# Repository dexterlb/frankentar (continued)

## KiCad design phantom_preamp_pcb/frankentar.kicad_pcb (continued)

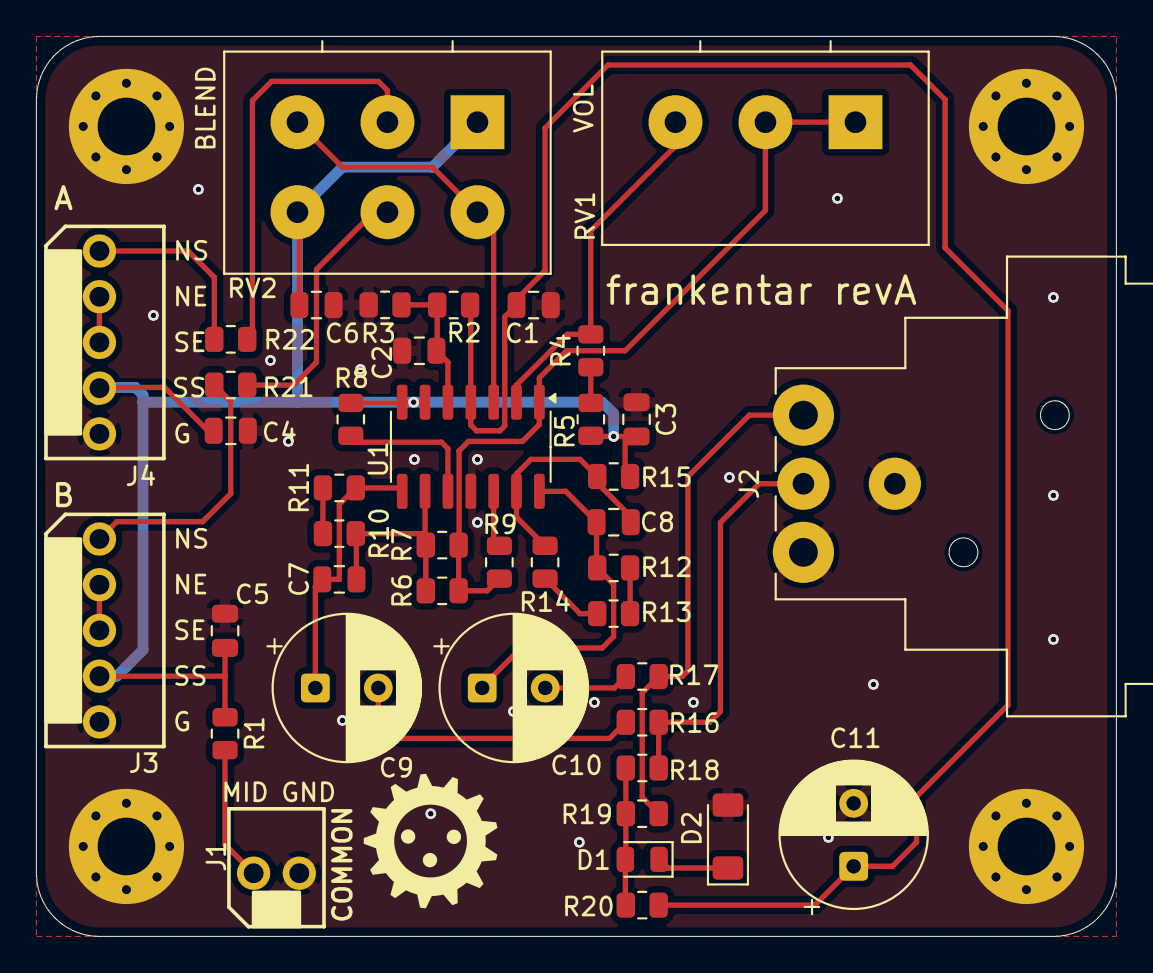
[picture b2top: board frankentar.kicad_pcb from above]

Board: 2 copper layers, 60.0 x 50.0 mm, 48 parts (1 on the bottom side), 30 nets.

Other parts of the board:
H5, H6: MountingHole_Pad; MountingHole_3.2mm_M3_Pad_Via

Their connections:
GND: H5.1, H6.1; also elsewhere on the board

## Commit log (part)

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2024-12-25 initial
2024-12-25 add gitignore and mta100 library
2024-12-25 add phantom-powered preamp schematic
2024-12-25 update libs
2024-12-25 add simulation
2024-12-25 some stuff
2025-01-03 arrange board
2025-06-13 update pcb
2025-06-20 final version
2025-11-04 pickup holder
2025-11-06 add preamp holder
2025-11-06 thicker nuts
2025-12-30 finalise preamp holder
